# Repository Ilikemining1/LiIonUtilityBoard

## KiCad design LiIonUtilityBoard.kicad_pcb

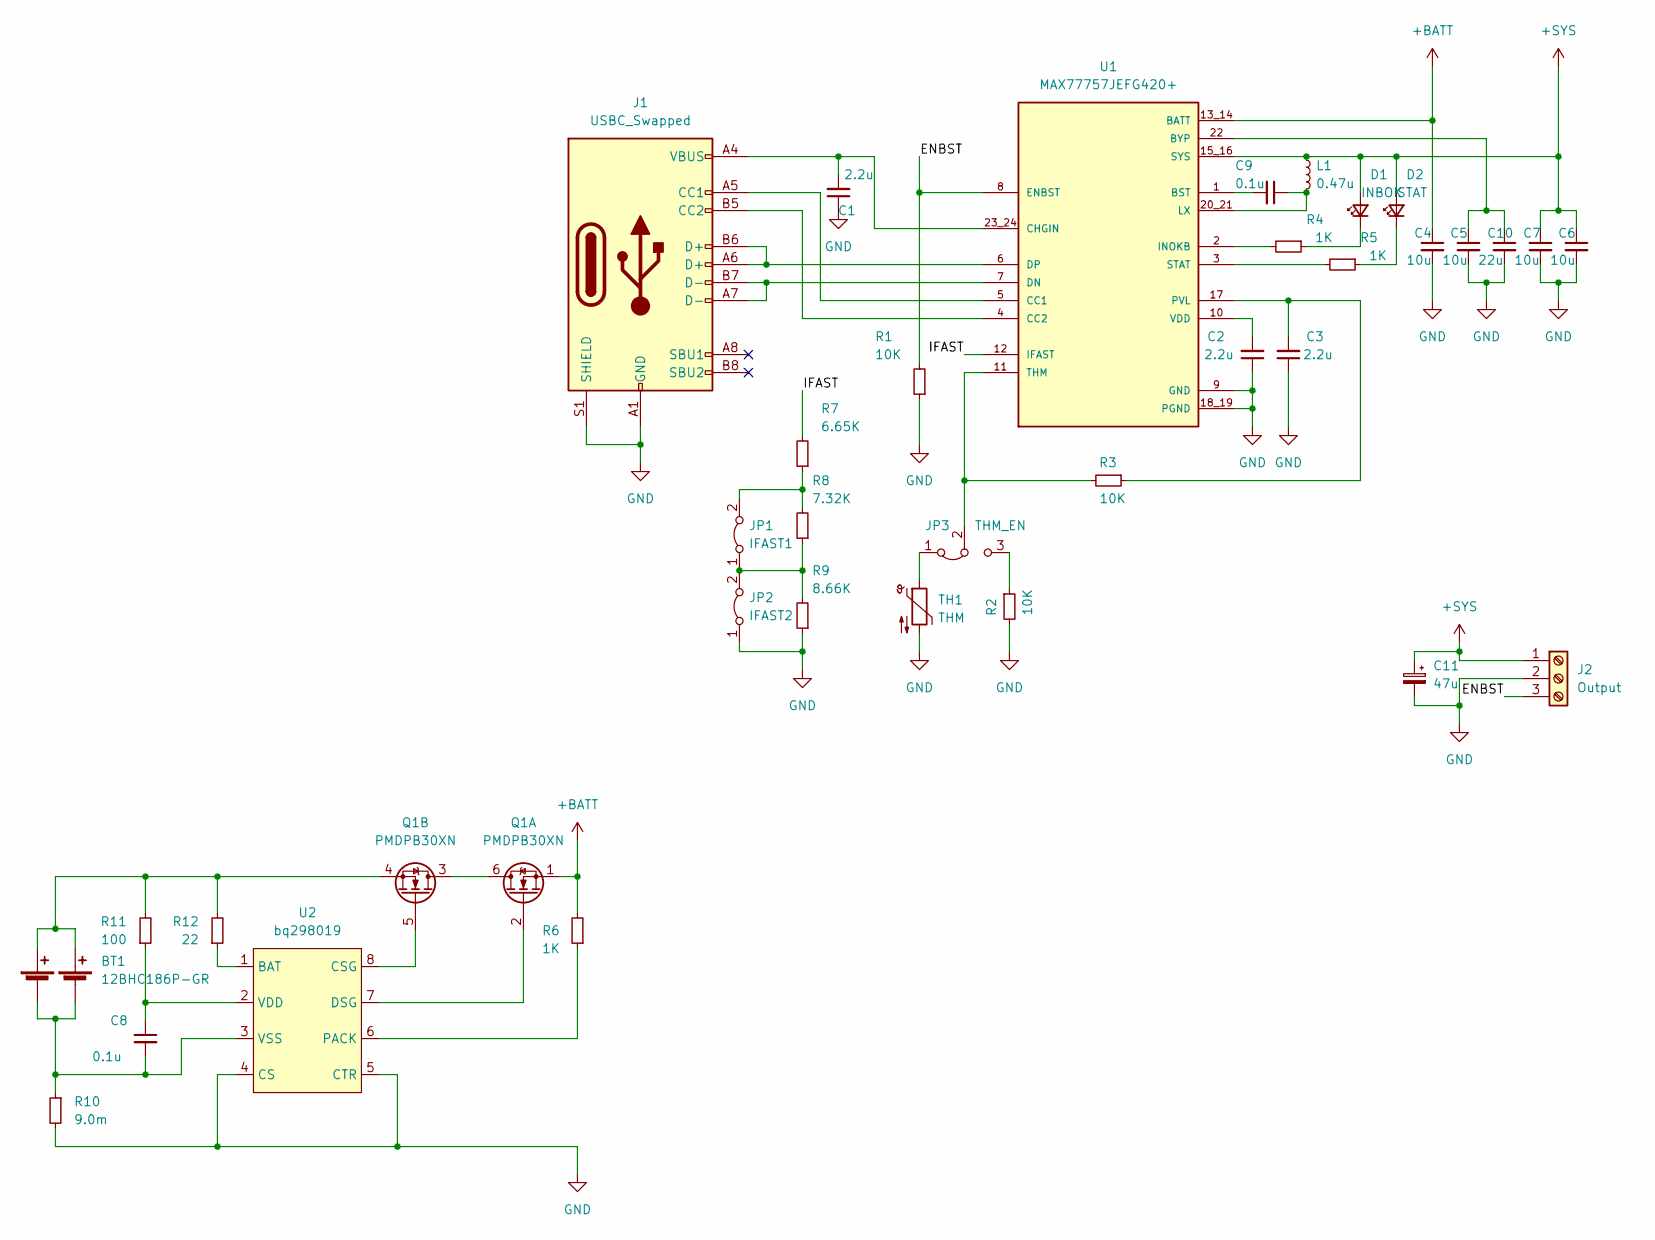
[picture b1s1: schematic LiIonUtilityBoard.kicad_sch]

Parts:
BT1: 12BHC186P-GR
C1, C2, C3: 2.2u; C_0402_1005Metric
C4, C5, C6, C7: 10u; C_0603_1608Metric
C8, C9: 0.1u; C_0402_1005Metric
C10: 22u; C_0805_2012Metric
C11: 47u; CP_Elec_5x5.3
D1: INBOK; LED_0603_1608Metric
D2: STAT; LED_0603_1608Metric
J1: USBC_Swapped; USB_C_Receptacle_GCT_USB4085
J2: Output; CUI_TB002-500-03BE
JP1: IFAST1; SolderJumper-2_P1.3mm_Bridged_Pad1.0x1.5mm
JP2: IFAST2; SolderJumper-2_P1.3mm_Bridged_Pad1.0x1.5mm
JP3: THM_EN; SolderJumper-3_P1.3mm_Bridged12_Pad1.0x1.5mm_NumberLabels
L1: 0.47u; L_1008_2520Metric
Q1: PMDPB30XN; SON65P200X200X65-8N
R1, R2, R3: 10K; R_0402_1005Metric
R4, R5, R6: 1K; R_0402_1005Metric
R7: 6.65K; R_0402_1005Metric
R8: 7.32K; R_0402_1005Metric
R9: 8.66K; R_0402_1005Metric
R10: 9.0m; R_0603_1608Metric
R11: 100; R_0402_1005Metric
R12: 22; R_0402_1005Metric
TH1: THM; PinHeader_1x02_P2.54mm_Vertical
U1: MAX77757JEFG420+; IC_MAX77757JEFG420+
U2: bq298019; BQ298009RUGR

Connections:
+BATT: C4.1, Q1.1 (S1), R6.2, U1.13_14 (BATT)
+SYS: C6.1, C7.1, C11.1, D1.2 (A), D2.2 (A), J2.1, L1.1, U1.15_16 (SYS)
/ENBST: J2.3, R1.2, U1.8 (ENBST)
/IFAST: R7.2, U1.12 (IFAST)
GND: C1.1, C2.1, C3.1, C4.2, C5.2, C6.2, C7.2, C10.2, C11.2, J1.A1 (GND), J1.A12 (GND), J1.B1 (GND), J1.B12 (GND), J1.S1 (SHIELD), J2.2, JP2.1 (A), R1.1, R2.2, R9.1, R10.2, TH1.2, U1.9 (GND), U1.18_19 (PGND), U2.4 (CS), U2.5 (CTR)
unnamed: BT1.1 (1+), BT1.3 (2+), Q1.4 (S2), R11.2, R12.2
unnamed: BT1.2 (1-), BT1.4 (2-), C8.2, R10.1, U2.3 (VSS)
unnamed: C1.2, J1.A4 (VBUS), J1.A9 (VBUS), J1.B4 (VBUS), J1.B9 (VBUS), U1.23_24 (CHGIN)
unnamed: C2.2, U1.10 (VDD)
unnamed: C3.2, R3.1, U1.17 (PVL)
unnamed: C8.1, R11.1, U2.2 (VDD)
unnamed: C9.1, L1.2, U1.20_21 (LX)
unnamed: C9.2, U1.1 (BST)
unnamed: C5.1, C10.1, U1.22 (BYP)
unnamed: D1.1 (K), R4.1
unnamed: D2.1 (K), R5.1
unnamed: J1.A5 (CC1), U1.5 (CC1)
unnamed: J1.A6 (D+), J1.B6 (D+), U1.6 (DP)
unnamed: J1.A7 (D-), J1.B7 (D-), U1.7 (DN)
unnamed: J1.B5 (CC2), U1.4 (CC2)
unnamed: JP1.1 (A), JP2.2 (B), R8.1, R9.2
unnamed: JP1.2 (B), R7.1, R8.2
unnamed: JP3.1 (A), TH1.1
unnamed: JP3.2 (C), R3.2, U1.11 (THM)
unnamed: JP3.3 (B), R2.1
unnamed: Q1.2 (G1), U2.7 (DSG)
unnamed: Q1.3 (D2), Q1.6 (D1), Q1.7 (D1), Q1.8 (D2)
unnamed: Q1.5 (G2), U2.8 (CSG)
unnamed: R4.2, U1.2 (INOKB)
unnamed: R5.2, U1.3 (STAT)
unnamed: R6.1, U2.6 (PACK)
unnamed: R12.1, U2.1 (BAT)

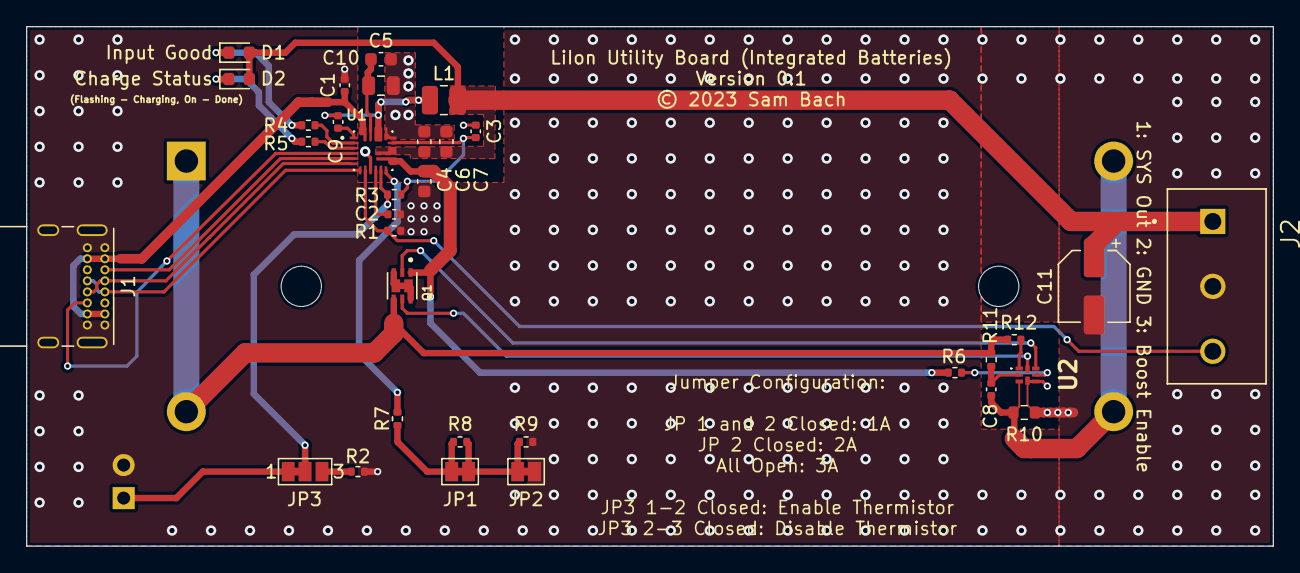
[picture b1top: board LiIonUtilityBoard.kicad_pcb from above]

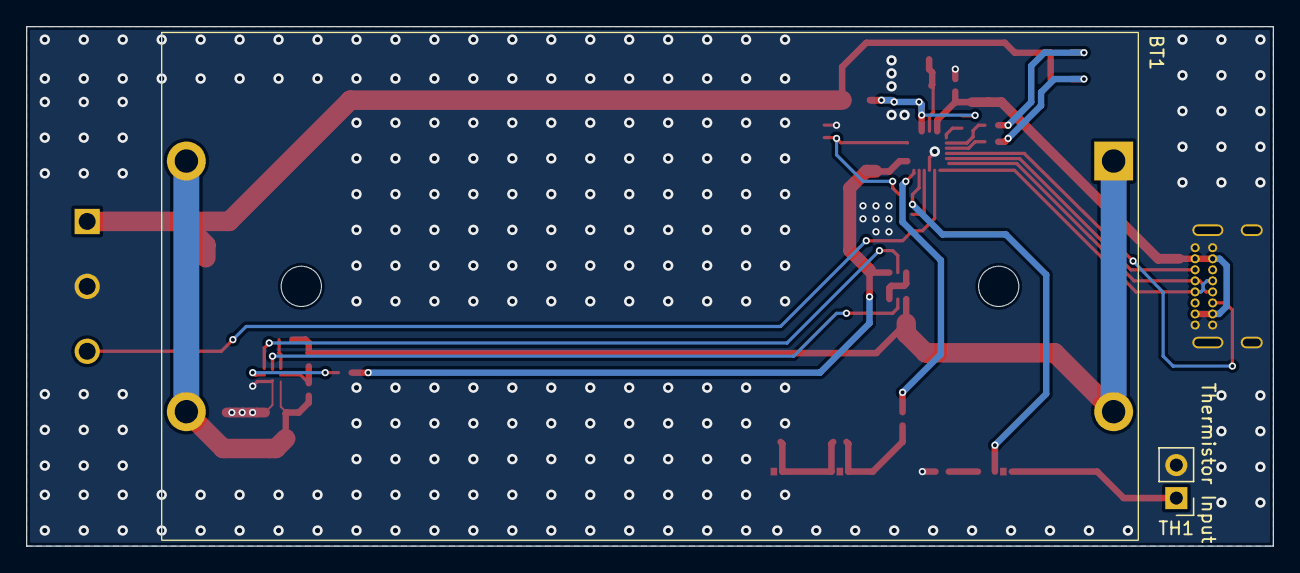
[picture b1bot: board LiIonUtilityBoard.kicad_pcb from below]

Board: 2 copper layers, 96.0 x 40.0 mm, 36 parts (2 on the bottom side), 32 nets.

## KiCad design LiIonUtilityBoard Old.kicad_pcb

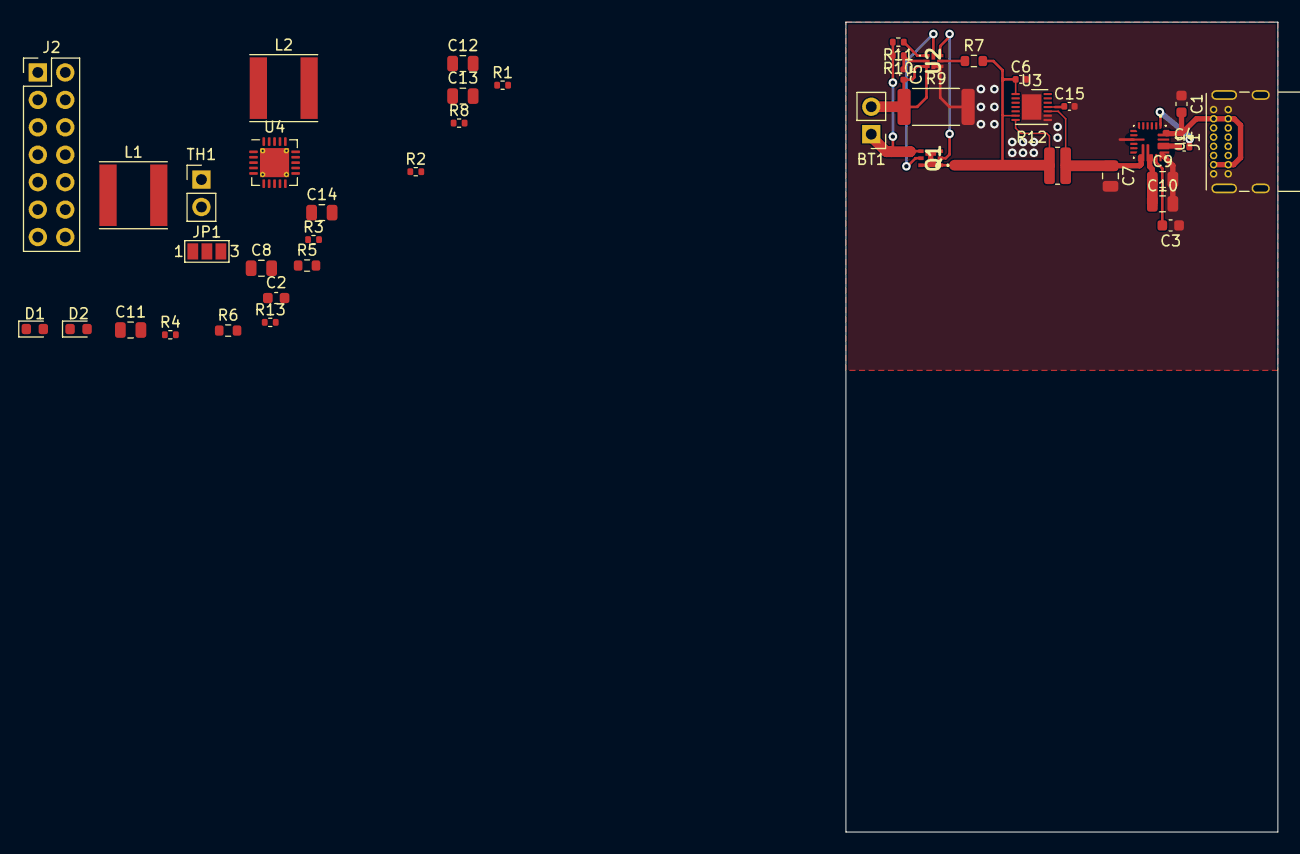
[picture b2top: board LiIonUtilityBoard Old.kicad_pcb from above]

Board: 2 copper layers, 40.0 x 75.0 mm, 42 parts (0 on the bottom side), 40 nets.

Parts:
BT1: BATT; PinHeader_1x02_P2.54mm_Vertical
C1, C2, C3: 2.2u; C_0603_1608Metric
C4, C5, C6: 0.1u; C_0402_1005Metric
C7, C8, C9, C10, C11: 10u; C_0805_2012Metric
C12, C13, C14: 22u; C_0805_2012Metric
C15: 0.47u; C_0402_1005Metric
D1: INBOK; LED_0603_1608Metric
D2: STAT; LED_0603_1608Metric
J1: USBC_Swapped; USB_C_Receptacle_GCT_USB4085
J2: Conn_02x07_Odd_Even; PinHeader_2x07_P2.54mm_Vertical
JP1: Jumper_3_Bridged12; SolderJumper-3_P1.3mm_Open_Pad1.0x1.5mm_NumberLabels
L1, L2: 1u; L_Taiyo-Yuden_NR-60xx
Q1: PMDPB30XN; DMN1025UFDB7
R1, R2, R3, R4, R13: 10K; R_0402_1005Metric
R5, R6, R7: 1K; R_0603_1608Metric
R8: 18.2K; R_0402_1005Metric
R9: 2.26m; R_2512_6332Metric
R10: 100; R_0402_1005Metric
R11: 22; R_0402_1005Metric
R12: 10m; R_0612_1632Metric
TH1: THM; PinHeader_1x02_P2.54mm_Vertical
U1: MAX77757JEFG420+; IC_MAX77757JEFG420+
U2: bq298215; BQ298009RUGR
U3: MAX17260SETD; TDFN-14-1EP_3x3mm_P0.4mm_EP1.78x2.35mm
U4: ISL91127IR; QFN-20-1EP_4x4mm_P0.5mm_EP2.7x2.7mm_ThermalVias

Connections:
+3V3: C13.1, C14.1, J2.1, J2.2, U4.15 (FB), U4.17 (VOUT), U4.18 (VOUT), U4.19 (VOUT), U4.20 (VOUT)
+BATT: C7.1, R12.2, U1.13_14 (BATT), U3.10 (CSPH)
+SYS: C9.1, C10.1, C11.1, D1.2 (A), D2.2 (A), J2.3, J2.4, L1.1, U1.15_16 (SYS), U4.6 (PVIN), U4.7 (PVIN), U4.8 (PVIN), U4.9 (PVIN), U4.10 (VIN)
/ENBST: J2.5, R1.2, U1.8 (ENBST)
/FG_ALRT: J2.6, U3.12 (ALRT)
/FG_SCL: J2.7, U3.14 (SCL)
/FG_SDA: J2.8, U3.13 (SDA)
/PFM_PWM: J2.9, R4.2, U4.12 (MODE)
/PWR: J2.10, R13.2, U4.11 (EN)
GND: C1.1, C2.1, C3.1, C6.2, C7.2, C8.2, C9.2, C10.2, C11.2, C12.2, C13.2, C14.2, C15.2, J1.A1 (GND), J1.A12 (GND), J1.B1 (GND), J1.B12 (GND), J1.S1 (SHIELD), J2.11, J2.12, J2.13, J2.14, R1.1, R2.2, R4.1, R8.1, R9.2, R13.1, TH1.2, U1.9 (GND), U1.18_19 (PGND), U2.4 (CS), U2.5 (CTR), U3.8 (GND), U3.9 (CSPL), U3.15 (GND), U4.3 (PGND), U4.13 (SGND), U4.14 (SGND), U4.21 (PGND)
unnamed: BT1.1 (+), Q1.4 (S2), R10.2, R11.2
unnamed: BT1.2 (-), C5.2, R9.1, U2.3 (VSS)
unnamed: C1.2, J1.A4 (VBUS), J1.A9 (VBUS), J1.B4 (VBUS), J1.B9 (VBUS), U1.23_24 (CHGIN)
unnamed: C2.2, U1.10 (VDD)
unnamed: C3.2, R3.1, U1.17 (PVL)
unnamed: C4.1, L1.2, U1.20_21 (LX)
unnamed: C4.2, U1.1 (BST)
unnamed: C5.1, R10.1, U2.2 (VDD)
unnamed: C6.1, Q1.1 (S1), R7.2, R12.1, U3.1 (TH), U3.6 (BATT), U3.7 (CSN)
unnamed: C8.1, C12.1, U1.22 (BYP)
unnamed: C15.1, U3.11 (REG)
unnamed: D1.1 (K), R5.1
unnamed: D2.1 (K), R6.1
unnamed: J1.A5 (CC1), U1.5 (CC1)
unnamed: J1.A6 (D+), J1.B6 (D+), U1.6 (DP)
unnamed: J1.A7 (D-), J1.B7 (D-), U1.7 (DN)
unnamed: J1.B5 (CC2), U1.4 (CC2)
unnamed: JP1.1 (A), TH1.1
unnamed: JP1.2 (C), R3.2, U1.11 (THM)
unnamed: JP1.3 (B), R2.1
unnamed: L2.1, U4.4 (LX1), U4.5 (LX1)
unnamed: L2.2, U4.1 (LX2), U4.2 (LX2)
unnamed: Q1.2 (G1), U2.7 (DSG)
unnamed: Q1.3 (D2), Q1.6 (D1), Q1.7 (D1), Q1.8 (D2)
unnamed: Q1.5 (G2), U2.8 (CSG)
unnamed: R5.2, U1.2 (INOKB)
unnamed: R6.2, U1.3 (STAT)
unnamed: R7.1, U2.6 (PACK)
unnamed: R8.2, U1.12 (IFAST)
unnamed: R11.1, U2.1 (BAT)

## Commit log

2022-12-28 Add KiCad gitignore
2022-12-29 Mostly finish schematic
2022-12-29 Begin PCB Layout
2023-01-09 Sync project status
2023-01-09 Finalize Schematic
2023-01-09 Finshed schematic and associated footprints
2023-01-10 Finish Routing
2023-01-10 Final Rev 0.1 PCB
2023-01-10 Export Gerbers

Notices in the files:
LiIonUtilityBoard.kicad_pcb:
© 2023 Sam Bach
